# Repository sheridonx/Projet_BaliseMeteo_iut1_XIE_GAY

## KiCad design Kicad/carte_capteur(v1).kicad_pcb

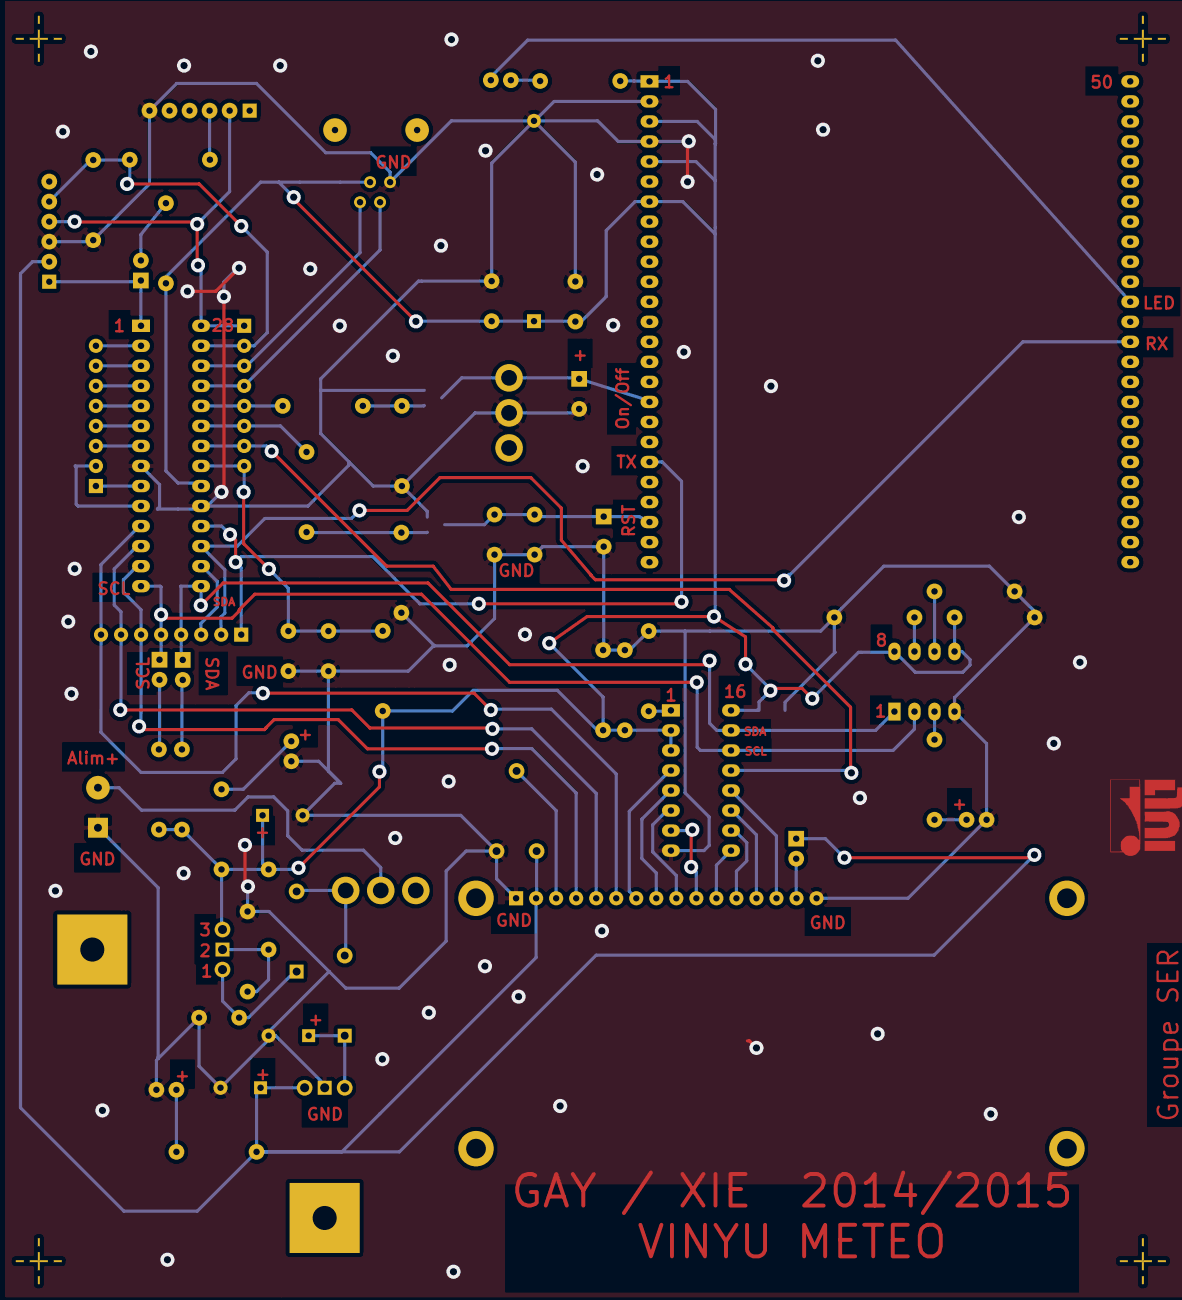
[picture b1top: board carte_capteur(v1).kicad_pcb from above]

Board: 2 copper layers, 70 parts (0 on the bottom side), 60 nets.

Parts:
C1, C4, C5: 100n; SM1206
C2: 470n; Tom_C1V8_2pas
C3: 22u; Tom_C1V8_2pas
C6, C12: 100n; Tom_C2
C7: 1u; Tom_C1V8_2pas
C8, C9: 100n; Tom_Cpola
C10: 1000u; CP10
C11: 4.7u; Tom_C2
D1, D4: DIODE; Tom_Diode
D2: LED Verte; Tom_LED-5MM
D3: LED Rouge; Tom_LED-5MM
D5: LED Bleu; Tom_LED-5MM
D6: LED; Tom_LED-5MM
JP6, JP7, JP8, JP9: JUMPER; Tom_SIL-2
LCD1: LCD_1602; Tom_LCD_1
MIRE: *; MIRE
MIRE#2, MIRE#3, MIRE#4: *; MIRE
P1: CONN_2; Tom_bornier2
P2, P7: CONN_6; Tom_SIL-6
P3: CONN_4; Tom_RJ11
P4, P5, P6: CONN_8; Tom_SIL-8
Q1, Q2: BC847; SOT23
R1, R5: 470; Tom_R4
R2, R14, R20: 1.2k; Tom_R4
R3: 487; Tom_R4
R4, R6, R7, R8, R9, R10, R11, R15, R16, R22: 10k; Tom_R4
R12: 237; Tom_R4
R13, R21: 330; Tom_R4
R17, R18: 47k; Tom_R4
R19: 1.5k; Tom_R4
RV1: POT; Tom_RV2X4
SW1, SW4: SPST; Tom_Interrupt1_IUT
SW5, SW6: SW_PUSH; Tom_SW1
U1: PIC18F2XK22; DIP-28__300_ELL
U2: LM2940; Tom_LM78XX_Horiz
U3: DS1621; DIP-8__300_ELL
U4: PCF8574; DIP-16__300_ELL
U5: TOM_TELIT862_CONN50; Modem_gsm_862
U6: LM317; Tom_LM317_Horiz
VAL: Logo IUT1 V3

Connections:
+5V: C3.1, JP7.1, LCD1.2, P2.2, R1.1, RV1.3, U2.VO
+BATT: C2.1, D1.2, U2.VI
/A0: R4.1, U3.7
/A1: R6.1, U3.6
/A10: R9.1, U4.1
/DB0: LCD1.7, U4.4
/DB1: LCD1.8, U4.5
/DB2: LCD1.9, U4.6
/DB3: LCD1.10, U4.7
/DB4: LCD1.11, U4.9
/DB5: LCD1.12, U4.10
/DB6: LCD1.13, U4.11
/DB7: LCD1.14, U4.12
/E_LCD: LCD1.6, P6.8, U1.11
/INT_LCD: P5.7, U1.22, U4.13
/ON/OFF: P5.5, R15.1, U1.24
/ONOFF: C8.1, Q1.3, SW4.2, U5.17
/PGC: P2.5, P5.2, R19.2, R20.2, U1.27
/PGD: P2.4, P5.1, P7.2, U1.28
/R/W_LCD: LCD1.5, P6.7, U1.12
/RE3: JP6.1, P2.1, U1.1
/REG: P3.2, P5.4, U1.25
/RS_LCD: LCD1.4, P6.6, U1.13
/RXGSM: P6.2, U1.17, U5.37
/Reset: P5.6, R16.1, U1.23
/Rst: C9.1, Q2.3, SW5.1, U5.23
/SCL: JP9.1, P6.5, U1.14, U3.2, U4.14
/SDA: JP8.1, P6.4, U1.15, U3.1, U4.15
/SW_choix: P5.8, R22.2, SW6.1, U1.21
/TOUT: R5.1, U3.3
/TXGSM: P6.1, U1.18, U5.20
/VENT: P3.4, P5.3, U1.26
GND: C1.2, C2.2, C3.2, C4.2, C5.2, C6.2, C7.2, C8.2, C9.2, C10.2, C11.2, C12.2, D2.2, D3.2, D5.2, LCD1.1, LCD1.16, P1.1, P2.3, P3.1, P7.6, Q1.2, Q2.2, R3.2, R4.2, R6.2, R7.2, R9.2, R10.2, R11.2, R17.2, R18.2, R19.1, RV1.1, SW4.1, SW5.2, SW6.2, U1.8, U1.19, U2.GND, U3.4, U4.8, U5.2, U5.4
unnamed: JP8.2, R2.2
unnamed: JP9.2, R14.2
unnamed: D1.1, D4.1, SW1.2
unnamed: P1.2, SW1.1
unnamed: D2.1, R1.2
unnamed: P4.1, U1.9
unnamed: LCD1.3, RV1.2
unnamed: JP6.2, R8.2
unnamed: JP7.2, LCD1.15
unnamed: D3.1, R5.2
unnamed: P4.2, U1.10
unnamed: P4.3, U1.7
unnamed: P4.4, U1.6
unnamed: P4.5, U1.5
unnamed: P4.7, U1.3
unnamed: P4.8, U1.2
unnamed: P6.3, U1.16
unnamed: P4.6, U1.4
unnamed: P7.3, R20.1
unnamed: C6.1, D4.2, U6.1
unnamed: R3.1, R12.2, U6.2
unnamed: D6.2, U5.39
unnamed: D6.1, R21.2
unnamed: D5.1, R13.2
unnamed: Q1.1, R15.2, R17.1
unnamed: Q2.1, R16.2, R18.1
VCC: C1.1, C4.1, C5.1, C7.1, C10.1, C11.1, C12.1, P3.3, R2.1, R7.1, R8.1, R10.1, R11.1, R12.1, R13.1, R14.1, R21.1, R22.1, U1.20, U3.5, U3.8, U4.2, U4.3, U4.16, U5.1, U5.3, U5.5, U5.7, U6.3

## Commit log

2015-04-09 :lollipop: Added .gitattributes
2015-04-09 Revert ":lollipop: Added .gitattributes"
    This reverts commit a9a7d84f191df13dd7064ebcdc850202abe53abb.
2015-04-09 Revert "Revert ":lollipop: Added .gitattributes""
    This reverts commit 425a29e4df1cfd733c7767b9bd582144598ccb9a.
2015-04-09 Revert "Revert "Revert ":lollipop: Added .gitattributes"""
    This reverts commit ce213976f4e446b199b1d917940ba4b5b6fd45ac.
2015-04-09 Revert "Revert "Revert "Revert ":lollipop: Added .gitattributes""""
    This reverts commit f254c24321ec0bb58745a16c51a9a9a32481020f.
2015-04-09 code 090415
2015-05-04 Routage sur Kicad
